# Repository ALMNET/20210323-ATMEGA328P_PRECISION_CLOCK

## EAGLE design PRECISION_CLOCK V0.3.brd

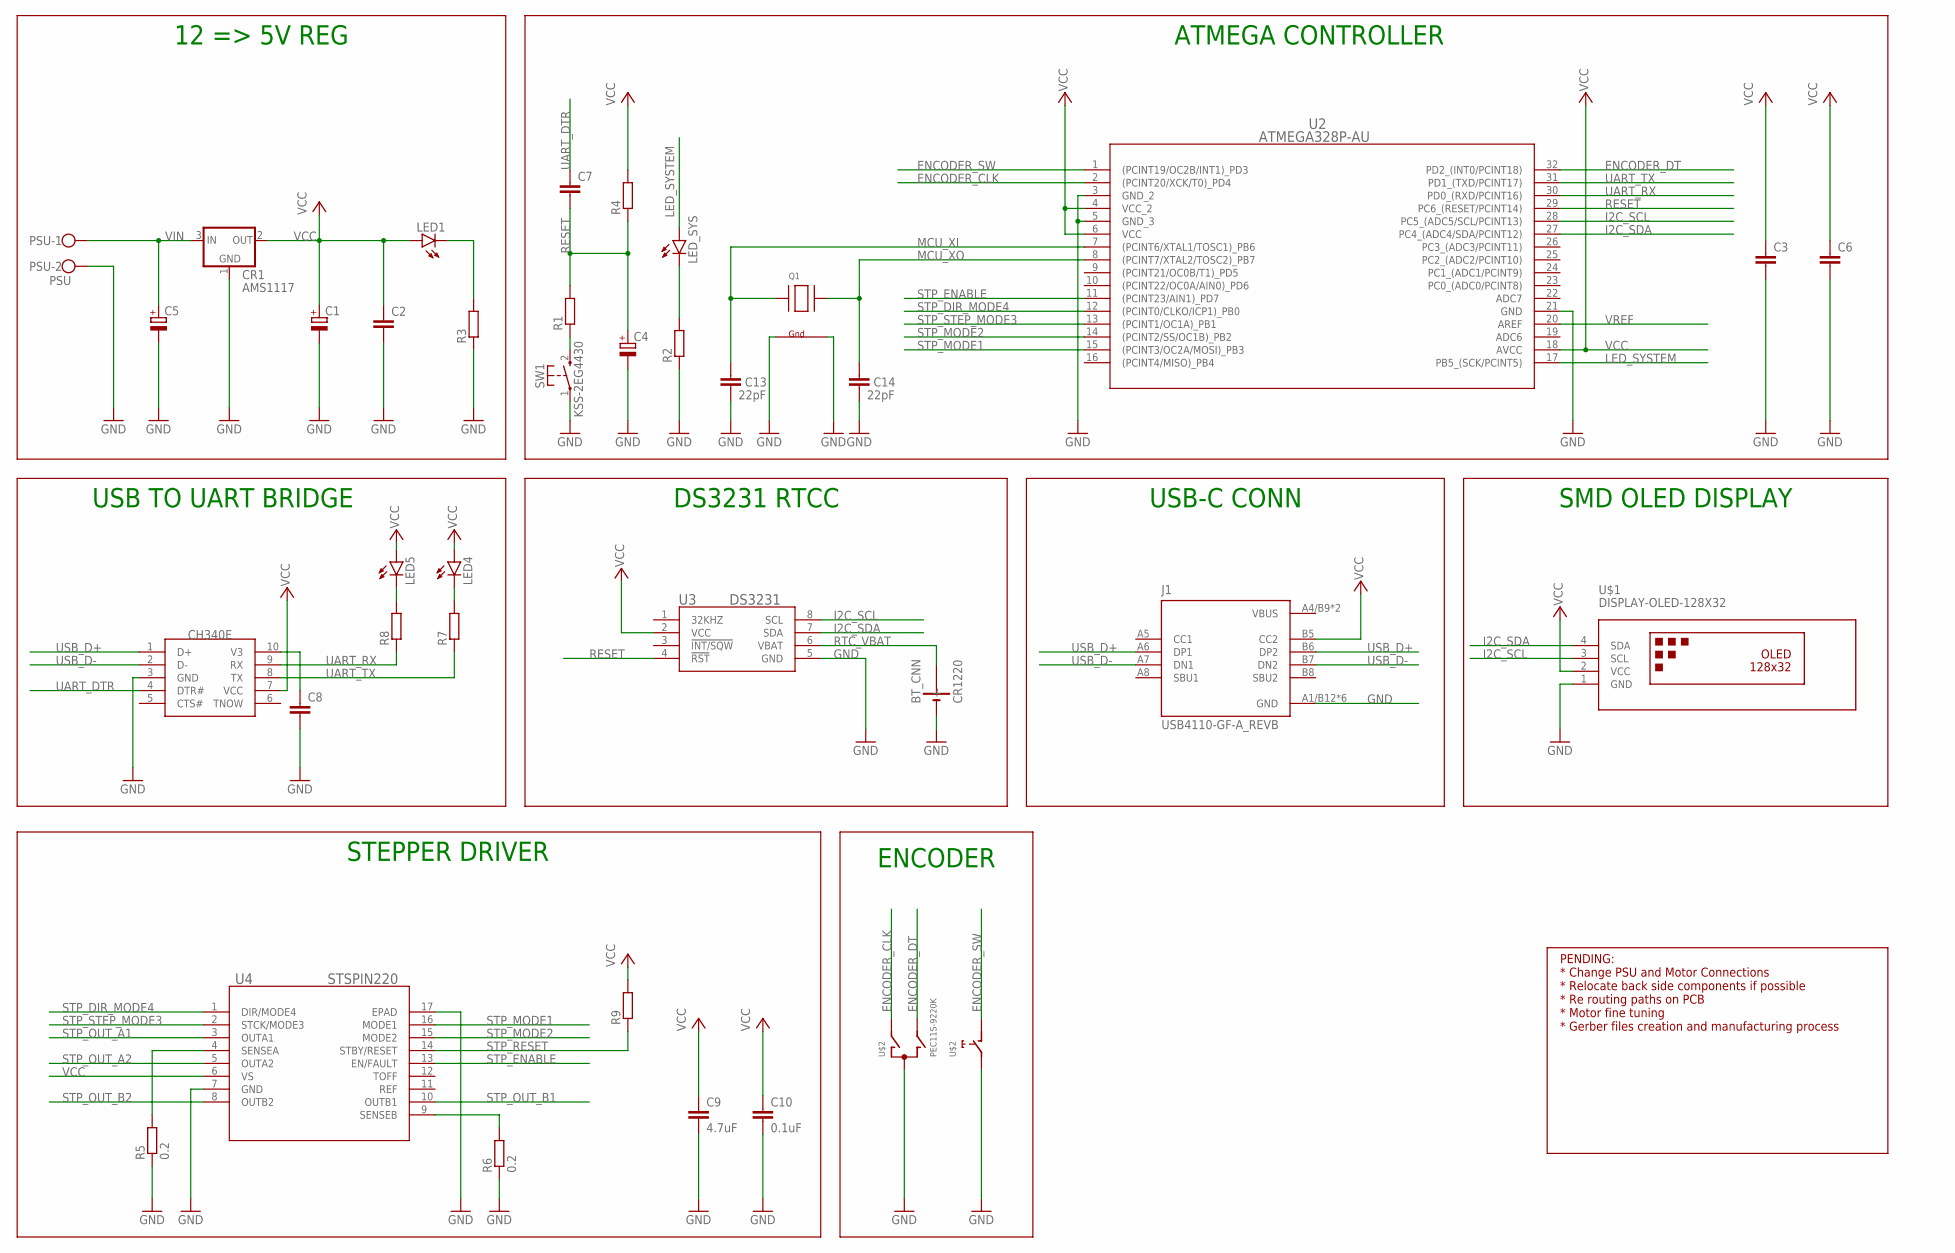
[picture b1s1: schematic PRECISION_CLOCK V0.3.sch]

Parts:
BT_CNN: CR1220; BH-44A-5
C1, C4, C5: CPOL-EU153CLV-0505; 153CLV-0505
C2, C3, C6, C7, C8: C-EUC0805; C0805
C9: 4.7uF; C0805
C10: 0.1uF; C0805
C13, C14: 22pF; C0805
CR1: AMS1117; SOT223
J1: USB4110-GF-A_REVB; GCT_USB4110-GF-A_REVB
LED1, LED4, LED5: LEDSML0805; SML0805
LED_SYS: LEDSML0805; SML0805
PSU: PSU; W237-102
Q1: XTAL-4-3225; NX3225
R1, R2, R3, R4, R7, R8, R9: R-EU_R0805; R0805
R5, R6: 0.2; R0805
SW1: KSS-2EG4430
U2: ATMEGA328P-AU; 32A_ATM
U3: DS3231; 21-0041B_8_MXM
U4: STSPIN220; VFQFPN-16_STM
U$1: DISPLAY-OLED-128X32
U$2: PEC11S-9220K
U$5: CH340E; MSOP10

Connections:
ENCODER_CLK: U2.2 ((PCINT20/XCK/T0)_PD4), U$2.P$A (A)
ENCODER_DT: U2.32 (PD2_(INT0/PCINT18)), U$2.P$B (B)
ENCODER_SW: U2.1 ((PCINT19/OC2B/INT1)_PD3), U$2.P$D (D)
GND: BT_CNN.P$1 (-), C1.-, C2.2, C3.2, C4.-, C5.-, C6.2, C8.2, C9.2, C10.2, C13.2, C14.2, CR1.1 (GROUND), J1.A1/B12 (GND), J1.B1/A12 (GND), J1.S1 (GND), J1.S2 (GND), J1.S3 (GND), J1.S4 (GND), PSU.2, Q1.2 (G2), Q1.4 (G1), R2.1, R3.1, R5.1, R6.1, SW1.1, U2.3 (GND_2), U2.5 (GND_3), U2.21 (GND), U3.5 (GND), U4.7 (GND), U4.17 (EPAD), U$1.1 (GND), U$2.P$C (C), U$2.P$E (E), U$5.3 (GND)
I2C_SCL: U2.28 (PC5_(ADC5/SCL/PCINT13)), U3.8 (SCL), U$1.3 (SCL)
I2C_SDA: U2.27 (PC4_(ADC4/SDA/PCINT12)), U3.7 (SDA), U$1.4 (SDA)
LED_SYSTEM: LED_SYS.A, U2.17 (PB5_(SCK/PCINT5))
MCU_XI: C13.1, Q1.1 (X1), U2.7 ((PCINT6/XTAL1/TOSC1)_PB6)
MCU_XO: C14.1, Q1.3 (X2), U2.8 ((PCINT7/XTAL2/TOSC2)_PB7)
unnamed: LED_SYS.C, R2.2
unnamed: R5.2, U4.4 (SENSEA)
unnamed: LED1.C, R3.2
unnamed: R1.1, SW1.2 (S)
unnamed: R6.2, U4.9 (SENSEB)
unnamed: LED4.C, R7.2
unnamed: LED5.C, R8.2
unnamed: C8.1, U$5.10 (V3)
RESET: C4.+, C7.2, R1.2, R4.1, U2.29 (PC6_(RESET/PCINT14)), U3.4 (!RST)
RTC_VBAT: BT_CNN.P$2 (+), U3.6 (VBAT)
STP_DIR_MODE4: U2.12 ((PCINT0/CLKO/ICP1)_PB0), U4.1 (DIR/MODE4)
STP_ENABLE: U2.11 ((PCINT23/AIN1)_PD7), U4.13 (EN/FAULT)
STP_MODE1: U2.15 ((PCINT3/OC2A/MOSI)_PB3), U4.16 (MODE1)
STP_MODE2: U2.14 ((PCINT2/SS/OC1B)_PB2), U4.15 (MODE2)
STP_OUT_A1: U4.3 (OUTA1)
STP_OUT_A2: U4.5 (OUTA2)
STP_OUT_B1: U4.10 (OUTB1)
STP_OUT_B2: U4.8 (OUTB2)
STP_RESET: R9.1, U4.14 (STBY/RESET)
STP_STEP_MODE3: U2.13 ((PCINT1/OC1A)_PB1), U4.2 (STCK/MODE3)
UART_DTR: C7.1, U$5.4 (DTR#)
UART_RX: R8.1, U2.30 (PD0_(RXD/PCINT16)), U$5.9 (RX)
UART_TX: R7.1, U2.31 (PD1_(TXD/PCINT17)), U$5.8 (TX)
USB_D+: J1.A6 (DP1), J1.B6 (DP2), U$5.1 (D+)
USB_D-: J1.A7 (DN1), J1.B7 (DN2), U$5.2 (D-)
VBUS: J1.A4/B9 (VBUS), J1.B4/A9 (VBUS)
VCC: C1.+, C2.1, C3.1, C6.1, C9.1, C10.1, CR1.2 (OUT), J1.B5 (CC2), LED1.A, LED4.A, LED5.A, R4.2, R9.2, U2.4 (VCC_2), U2.6 (VCC), U2.18 (AVCC), U3.2 (VCC), U4.6 (VS), U$1.2 (VCC), U$5.7 (VCC)
VIN: C5.+, CR1.3 (IN), PSU.1
VREF: U2.20 (AREF)

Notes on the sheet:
12 => 5V REG
ATMEGA CONTROLLER
STEPPER DRIVER
USB TO UART BRIDGE
DS3231 RTCC
SMD OLED DISPLAY
PENDING: * Change PSU and Motor Connections * Relocate back side components if possible * Re routing paths on PCB * Motor fine tuning * Gerber files creation and manufacturing process
ENCODER
USB-C CONN

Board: 2 copper layers, 37 parts (16 on the bottom side), 33 nets, no tracks yet.

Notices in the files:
parts and their libraries:
diy-modules: Released under the Creative Commons Attribution 4.0 International License: http://creativecommons.org/licenses/by/4.0
COPYRIGHT: Copyright (C) 2018 Accelerated Designs. All rights reserved
